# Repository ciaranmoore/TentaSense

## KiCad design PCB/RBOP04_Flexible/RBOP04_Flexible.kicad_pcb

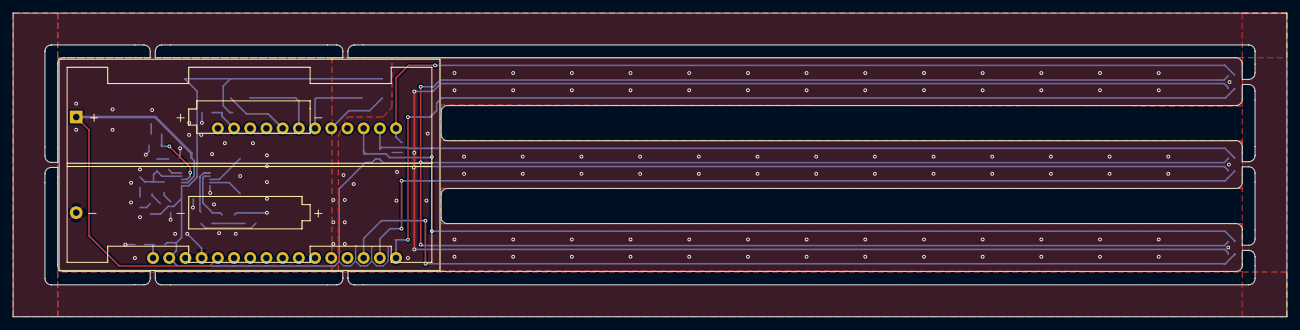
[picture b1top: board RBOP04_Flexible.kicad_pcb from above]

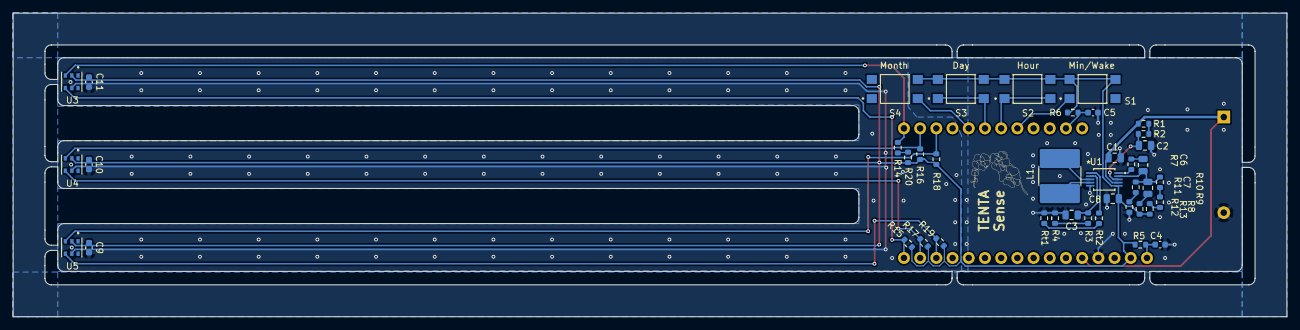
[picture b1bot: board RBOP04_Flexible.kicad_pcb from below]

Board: 2 copper layers, 199.7 x 47.6 mm, 44 parts (42 on the bottom side), 31 nets.

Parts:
B1: 2462; BatteryHolder_Keystone_2462_2xAA_CM
C1: 4.7u; C_0805_2012Metric
C2: 4.7n; C_0805_2012Metric
C3: 0.01u; C_0805_2012Metric
C4, C5: 1u; C_0603_1608Metric
C6, C7: 150p; C_0805_2012Metric
C8: 22u; C_0805_2012Metric
C9, C10, C11: 100n; C_0603_1608Metric
L1: 4.7u; L_2424_6060Metric
R1, R2, R3, R4, R11, R12: 100k; R_0603_1608Metric
R5, R6, R14, R15, R16, R17, R18, R19: 10k; R_0603_1608Metric
R7: 12k; R_0603_1608Metric
R8, R9: 150k; R_0603_1608Metric
R10: 22k; R_0603_1608Metric
R13: 1k; R_0603_1608Metric
R20: 0; R_0603_1608Metric
Rt1: 82k; R_0603_1608Metric
Rt2: 4.7k; R_0603_1608Metric
S1, S2, S3, S4: TL3305AF160QG; Button-CM
U1: LTC3532EMS-PBF; MSOP-10_MS_LIT
U2: THING_PLUS_LOGICAL; ESP32_Thing_Plus_C_hat
U3, U4, U5: AHT20; PSON100P300X300X110-6N

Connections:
!SHDN: C2.1, R2.2, U1.8 (*SHDN/SS)
DD: S3.1, S3.2, U2.6 (33)
GND: B1.1, C1.2, C2.2, C3.2, C4.2, C5.2, C8.2, C9.2, C10.2, C11.2, R4.2, R12.2, Rt1.2, U1.5 (GND), U2.25 (GND), U3.5 (GND), U4.5 (GND), U5.5 (GND)
HH: S2.1, S2.2, U2.7 (27)
MM: S4.2, U2.5 (15)
unnamed: C6.2, R7.1
unnamed: C7.1, R13.2
unnamed: R1.2, R2.1
unnamed: R3.2, R4.1
unnamed: R8.2, R9.1
unnamed: R9.2, R10.1
unnamed: R11.2, R12.1
unnamed: R14.1, R20.2
unnamed: Rt1.1, Rt2.2
unnamed: C3.1, R3.1, U1.2 (BURST)
unnamed: C6.1, C7.2, R10.2, R11.1, U1.9 (FB)
unnamed: Rt2.1, U1.1 (RT)
unnamed: L1.2, U1.3 (SW1)
unnamed: L1.1, U1.4 (SW2)
unnamed: R7.2, U1.10 (VC)
unnamed: C5.1, R6.2, U2.11 (EN)
unnamed: C4.1, R5.2, U2.28 (~RESET)
SCL1: R14.2, U2.1 (21/SDA), U3.3 (SCL)
SCL2: R16.2, U2.2 (22/SCL), U4.3 (SCL)
SCL3: R18.2, U2.3 (14), U5.3 (SCL)
SDA1: R15.1, U2.13 (4/FREE), U3.4 (SDA)
SDA2: R17.1, U2.14 (17/TX), U4.4 (SDA)
SDA3: R19.1, U2.15 (16/RX), U5.4 (SDA)
VDD: C8.1, C9.1, C10.1, C11.1, R5.1, R6.1, R8.1, R13.1, R15.2, R16.1, R17.2, R18.1, R19.2, R20.1, S1.3, S1.4, S2.3, S2.4, S3.3, S3.4, S4.4, U1.6 (VOUT), U2.27 (3.3V), U3.2 (VDD), U4.2 (VDD), U5.2 (VDD)
Vbatt: B1.2, C1.1, R1.1, U1.7 (VIN), U2.24 (26/A0)
mm: S1.1, U2.8 (12)

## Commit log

2024-07-01 Migration from eng-git to github.
